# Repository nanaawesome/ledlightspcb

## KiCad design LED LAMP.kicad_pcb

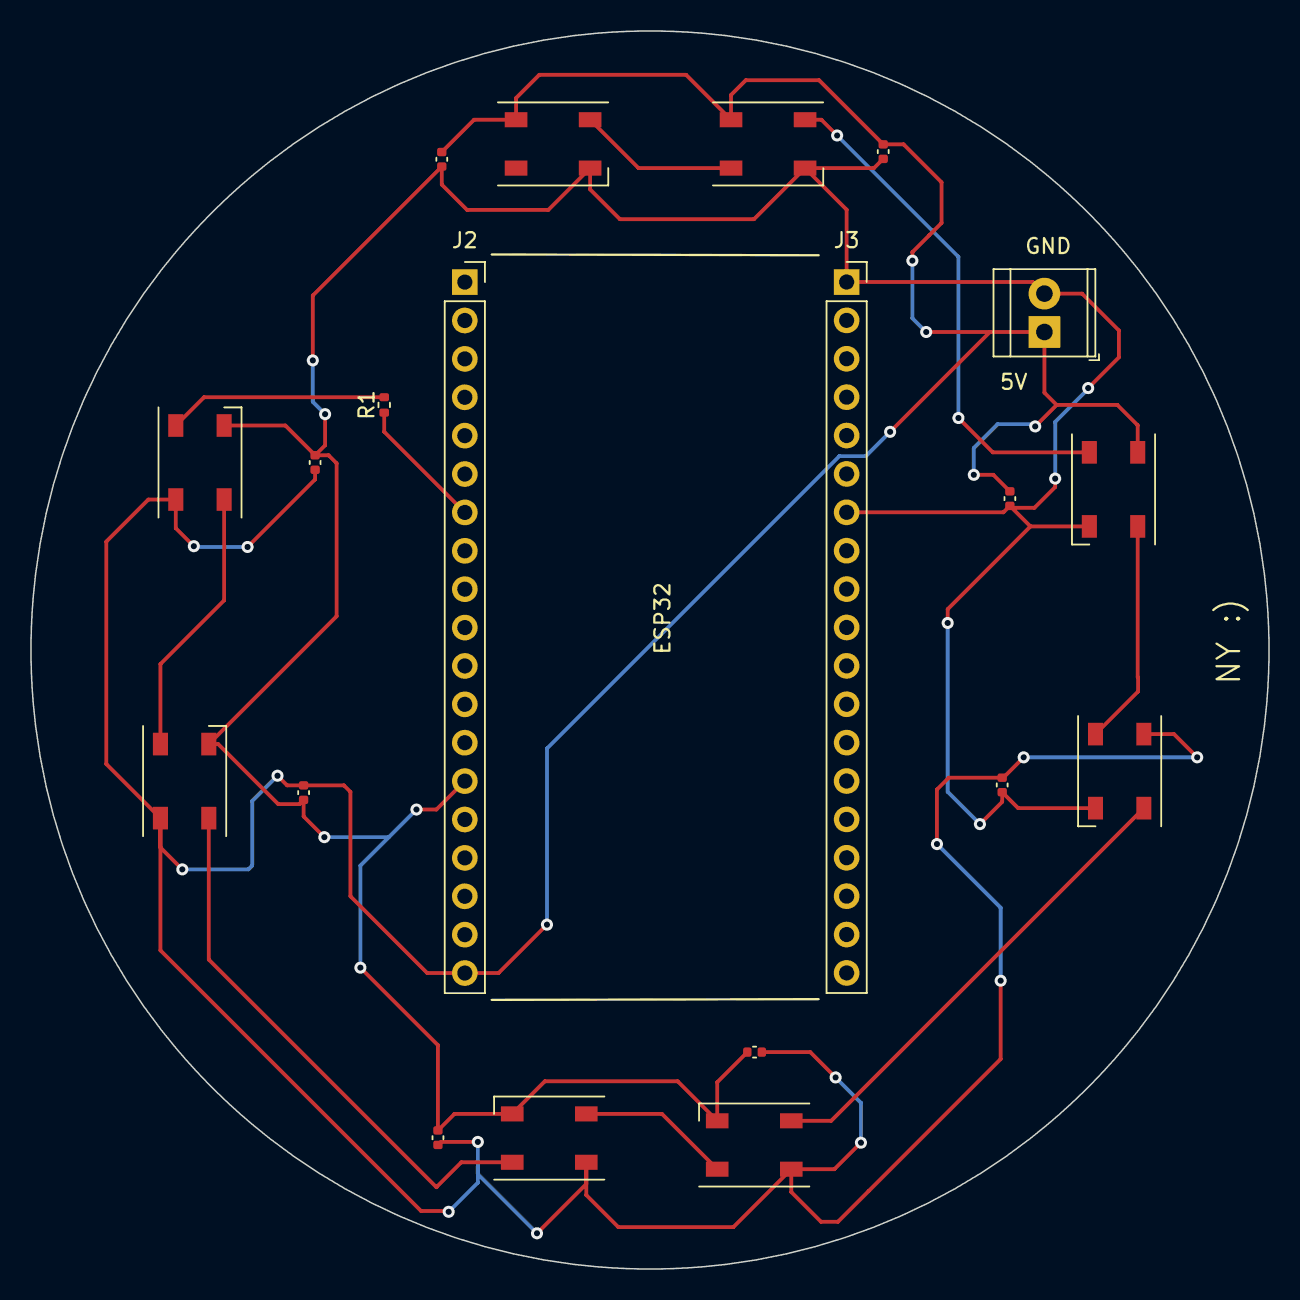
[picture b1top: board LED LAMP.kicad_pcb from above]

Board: 2 copper layers, 81.9 x 81.9 mm, 20 parts (0 on the bottom side), 11 nets.

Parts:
C1, C2, C3, C4, C5, C6, C7, C8: 0.39uF; C_0402_1005Metric
D1, D2, D3, D4, D5, D6, D7, D8: SK6812; LED_SK6812_PLCC4_5.0x5.0mm_P3.2mm
J1: Screw_Terminal_01x02; TerminalBlock_TE_282834-2_1x02_P2.54mm_Horizontal
J2, J3: Conn_01x19_Male; PinSocket_1x19_P2.54mm_Vertical
R1: 330Ω; R_0402_1005Metric

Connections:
+5V: C1.1, C2.1, C3.1, C4.1, C5.1, C6.1, C7.1, C8.1, D1.3 (VDD), D2.3 (VDD), D3.3 (VDD), D4.3 (VDD), D5.3 (VDD), D6.3 (VDD), D7.3 (VDD), D8.3 (VDD), J1.1, J2.19
/32: J2.7, R1.1
GND: C1.2, C2.2, C3.2, C4.2, C5.2, C6.2, C7.2, C8.2, D1.1 (VSS), D2.1 (VSS), D3.1 (VSS), D4.1 (VSS), D5.1 (VSS), D6.1 (VSS), D7.1 (VSS), D8.1 (VSS), J1.2, J2.14, J3.1, J3.7
unnamed: D1.2 (DIN), D4.4 (DOUT)
unnamed: D1.4 (DOUT), D8.2 (DIN)
unnamed: D2.2 (DIN), R1.2
unnamed: D2.4 (DOUT), D3.2 (DIN)
unnamed: D3.4 (DOUT), D5.2 (DIN)
unnamed: D4.2 (DIN), D7.4 (DOUT)
unnamed: D5.4 (DOUT), D6.2 (DIN)
unnamed: D6.4 (DOUT), D7.2 (DIN)
